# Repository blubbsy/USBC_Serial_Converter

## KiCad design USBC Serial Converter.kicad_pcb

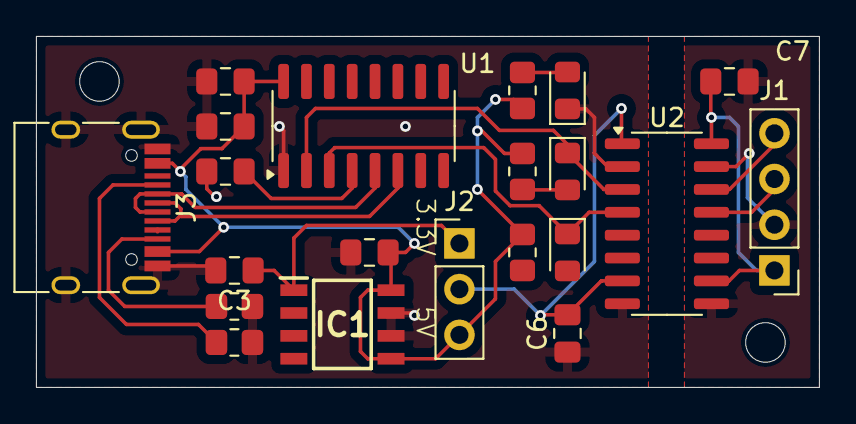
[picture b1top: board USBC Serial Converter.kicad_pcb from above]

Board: 2 copper layers, 43.5 x 19.5 mm, 23 parts (0 on the bottom side), 18 nets.

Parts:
C1: 10u; C_0805_2012Metric_Pad1.18x1.45mm_HandSolder
C2, C5, C6, C7: 0.1u; C_0805_2012Metric_Pad1.18x1.45mm_HandSolder
C3, C4: 1u; C_0805_2012Metric_Pad1.18x1.45mm_HandSolder
D1, D2, D3: LED; LED_0805_2012Metric_Pad1.15x1.40mm_HandSolder
H1, H1#2: MountingHole; MountingHole_2.2mm_M2_ISO7380
IC1: AP2112M-3.3TRG1; SOIC127P600X170-8N
J1: Conn_01x04_Pin; PinHeader_1x04_P2.54mm_Vertical
J2: Conn_01x03_Pin; PinHeader_1x03_P2.54mm_Vertical
J3: USB_C_Receptacle_USB2.0_16P; USB_C_Receptacle_HRO_TYPE-C-31-M-12
R1, R2: 5.1k; R_0805_2012Metric_Pad1.20x1.40mm_HandSolder
R3, R4, R5: 470; R_0805_2012Metric_Pad1.20x1.40mm_HandSolder
U1: CH340C; SOIC-16_3.9x9.9mm_P1.27mm
U2: Si8642BC-B-IS1; SOIC-16_3.9x9.9mm_P1.27mm

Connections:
+3.3V: C3.1, IC1.1 (VOUT), J2.1
+5V: C1.1, C2.1, C4.1, IC1.5 (EN), IC1.8 (VIN), J2.3, J3.A4 (VBUS), J3.A9 (VBUS), J3.B4 (VBUS), J3.B9 (VBUS), R3.2, R4.2, R5.2, U1.16 (VCC)
/RXD: D3.1 (K), U1.3 (RXD), U2.4 (A2)
/RXD_B: J1.3, U2.13 (B2)
/TXD: D2.1 (K), U1.2 (TXD), U2.3 (A1)
/TXD_B: J1.4, U2.14 (B1)
/USBD+: J3.A6 (D+), J3.B6 (D+), U1.6 (UD-)
/USBD-: J3.A7 (D-), J3.B7 (D-), U1.5 (UD+)
GND: C1.2, C2.2, C3.2, C4.2, C5.2, C6.1, D1.1 (K), IC1.6 (GND_1), IC1.7 (GND_2), J3.A1 (GND), J3.A12 (GND), J3.B1 (GND), J3.B12 (GND), J3.S1 (SHIELD), R1.1, R2.2, U1.1 (GND), U2.2 (GND1), U2.8 (GND1)
GND_B: C7.2, J1.2, U2.9 (GND2), U2.15 (GND2)
unnamed: D1.2 (A), R3.1
unnamed: D2.2 (A), R4.1
unnamed: D3.2 (A), R5.1
unnamed: J3.A5 (CC1), R2.1
unnamed: J3.B5 (CC2), R1.2
unnamed: C5.1, U1.4 (V3)
VCOM: C6.2, J2.2, U2.1 (VDD1), U2.7 (EN1)
VCOM_B: C7.1, J1.1, U2.10 (EN2), U2.16 (VDD2)

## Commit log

2025-01-02 first design
2025-01-12 added isolater for future
2025-01-24 added gitignore file
